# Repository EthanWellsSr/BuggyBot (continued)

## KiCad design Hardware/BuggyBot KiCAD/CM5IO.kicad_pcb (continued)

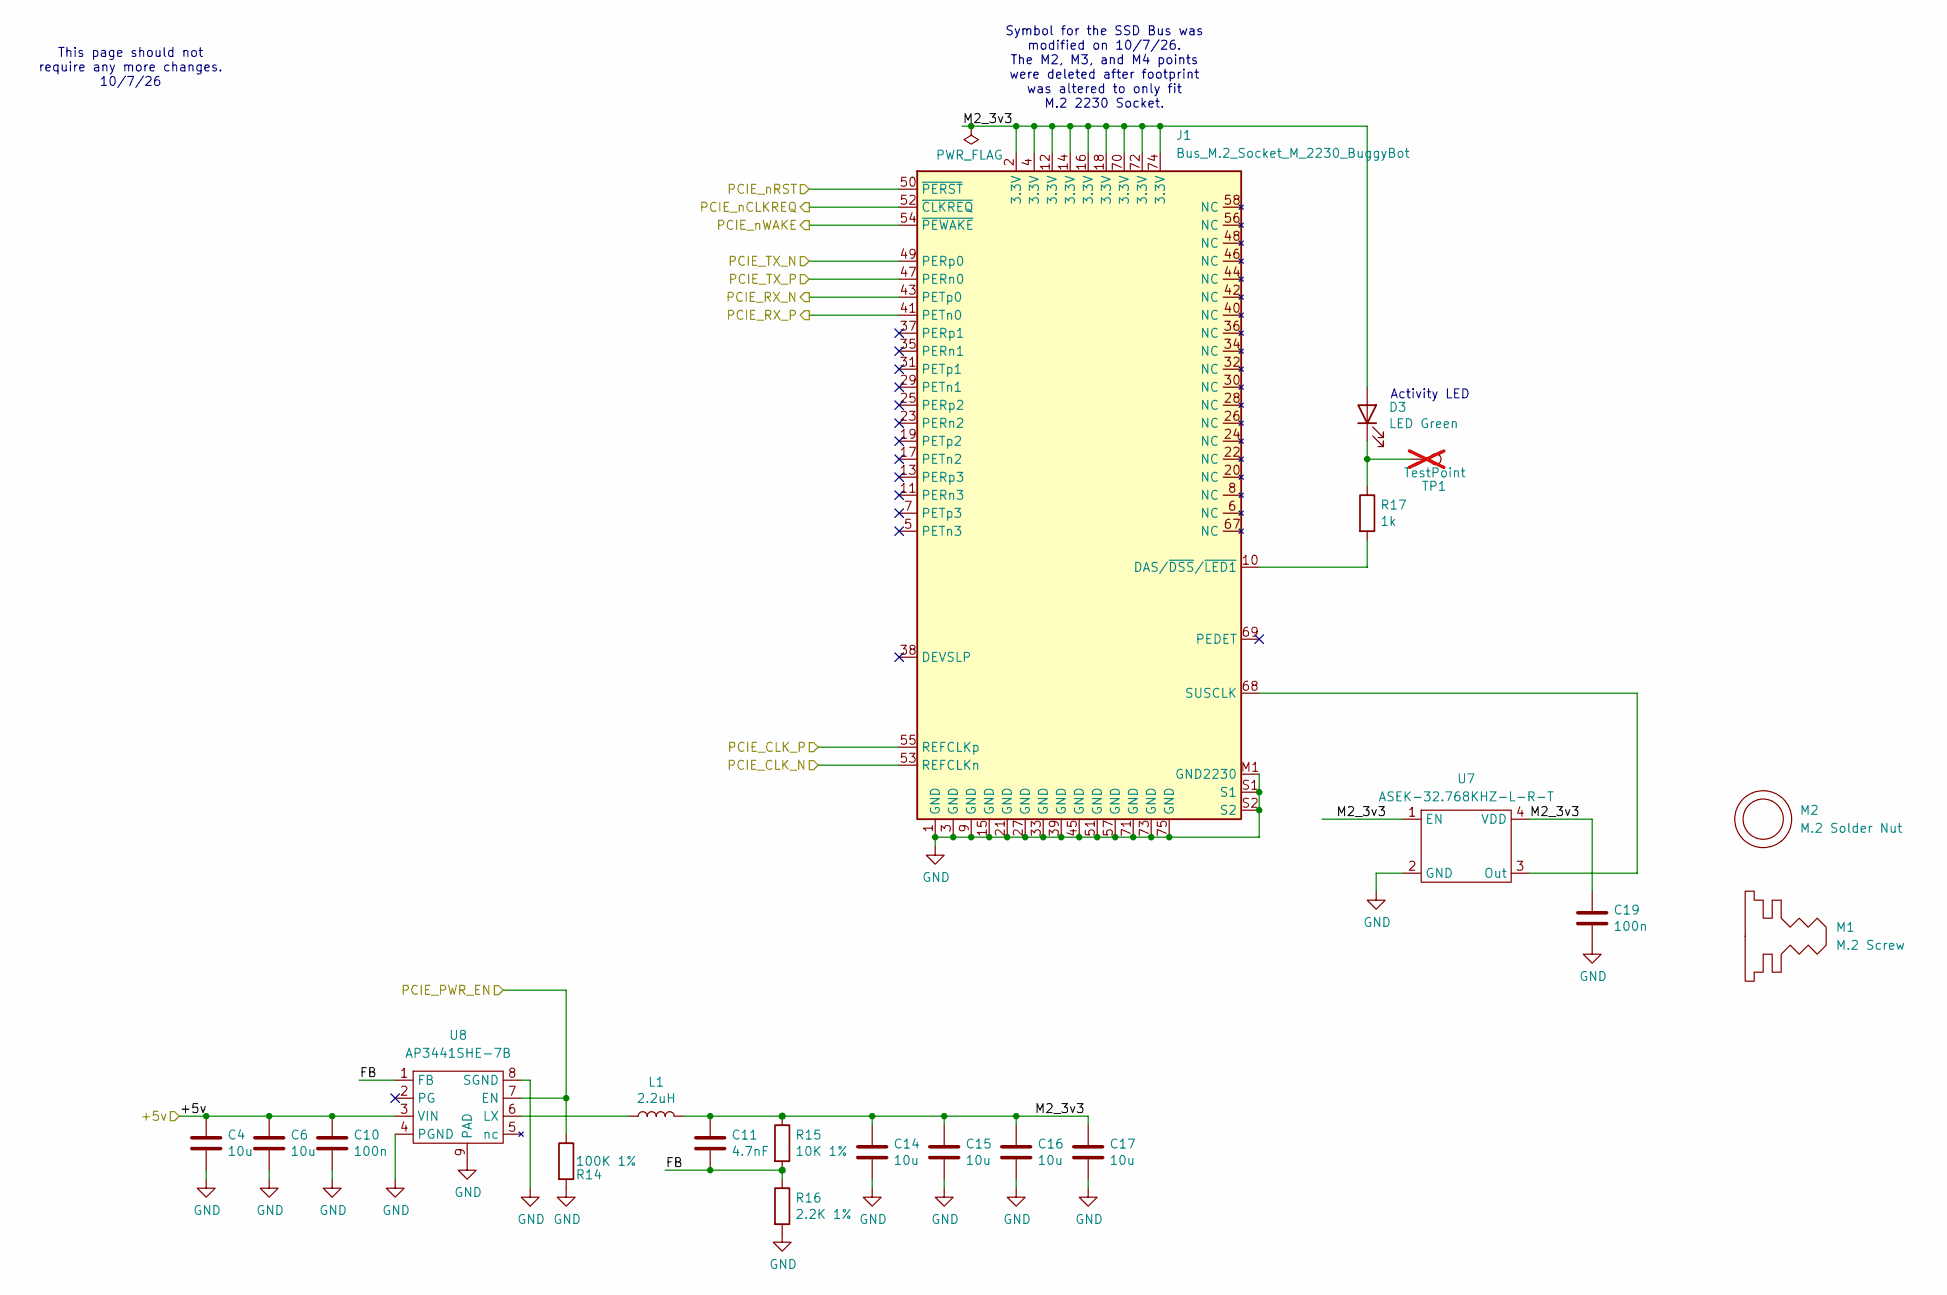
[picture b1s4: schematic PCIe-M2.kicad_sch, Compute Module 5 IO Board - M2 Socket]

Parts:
C4, C6, C14, C15, C16, C17: 10u; C_0805_2012Metric; Part Description 10uF 10% 10V Ceramic Capacitor X7R 0805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
C10, C19: 100n; C_0402_1005Metric; Part Description 0.1uF 10% 16V Ceramic Capacitor X7R 040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
C11: 4.7nF; C_0402_1005Metric; Part Description 4.7nF capacitor 0402
D3: LED Green; LED_0603_1608Metric; Part Description Green 572nm LED Indication - Discrete 2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
J1: Bus_M.2_Socket_M_2230_BuggyBot; M2_M_Key_2230_BuggyBot
L1: 2.2uH; L_Bourns_SRP5030CC; Part Description Inductor, SMT, 2520, 2u2, IRMS=7A, ISAT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
M1: M.2 Screw; Part Description M.2 Screw
M2: M.2 Solder Nut; Part Description Solder nut for M.2 slot
R14: 100K 1%; R_0402_1005Metric; Part Description Resistor 100K M1005 1% 63mW
R15: 10K 1%; R_0402_1005Metric; Part Description Resistor 10K M1005 1% 63mW
R16: 2.2K 1%; R_0402_1005Metric; Part Description Resistor 2.2K M1005 1% 63mW
R17: 1k; R_0402_1005Metric; Part Description Resistor 1K M1005 1% 63mW
TP1: TestPoint; TestPoint_Pad_2.0x2.0mm; Part Description Test point; not fitted
U7: ASEK-32.768KHZ-L-R-T; Crystal_SMD_3225-4Pin_3.2x2.5mm; Part Description 32KHz Xtal oscilator
U8: AP3441SHE-7B; DFN-8-1EP_2x2mm_P0.5mm_EP1.05x1.75mm; Part Description 3A DC-DC converter

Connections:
/+5v: C4.1, C6.1, C10.1, U8.3 (VIN); also elsewhere on the board
/CM5_HighSpeed/PCIE_CLK_N: J1.53 (REFCLKn); also elsewhere on the board
/CM5_HighSpeed/PCIE_CLK_P: J1.55 (REFCLKp); also elsewhere on the board
/CM5_HighSpeed/PCIE_PWR_EN: R14.1, U8.7 (EN); also elsewhere on the board
/CM5_HighSpeed/PCIE_RX_N: J1.43 (PETp0); also elsewhere on the board
/CM5_HighSpeed/PCIE_RX_P: J1.41 (PETn0); also elsewhere on the board
/CM5_HighSpeed/PCIE_TX_N: J1.49 (PERp0); also elsewhere on the board
/CM5_HighSpeed/PCIE_TX_P: J1.47 (PERn0); also elsewhere on the board
/CM5_HighSpeed/PCIE_nCLKREQ: J1.52 (~CLKREQ); also elsewhere on the board
/CM5_HighSpeed/PCIE_nRST: J1.50 (~PERST); also elsewhere on the board
/CM5_HighSpeed/PCIE_nWAKE: J1.54 (~PEWAKE); also elsewhere on the board
/PCIe-M2/FB: C11.2, R15.2, R16.1, U8.1 (FB)
/PCIe-M2/M2_3v3: C11.1, C14.1, C15.1, C16.1, C17.1, C19.1, D3.2 (A), J1.2 (3.3V), J1.4 (3.3V), J1.12 (3.3V), J1.14 (3.3V), J1.16 (3.3V), J1.18 (3.3V), J1.70 (3.3V), J1.72 (3.3V), J1.74 (3.3V), L1.2, R15.1, U7.1 (EN), U7.4 (VDD)
GND: C4.2, C6.2, C10.2, C14.2, C15.2, C16.2, C17.2, C19.2, J1.1 (GND), J1.3 (GND), J1.9 (GND), J1.15 (GND), J1.21 (GND), J1.27 (GND), J1.33 (GND), J1.39 (GND), J1.45 (GND), J1.51 (GND), J1.57 (GND), J1.71 (GND), J1.73 (GND), J1.75 (GND), J1.M1 (GND2230), J1.S1, J1.S2, R14.2, R16.2, U7.2 (GND), U8.4 (PGND), U8.8 (SGND), U8.9 (PAD); also elsewhere on the board
unnamed: D3.1 (K), R17.1, TP1.1 (1_1)
unnamed: J1.10 (DAS/~DSS/~LED1), R17.2
unnamed: J1.68 (SUSCLK), U7.3 (Out)
unnamed: L1.1, U8.6 (LX)

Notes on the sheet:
Symbol for the SSD Bus was modified on 10/7/26. The M2, M3, and M4 points were deleted after footprint was altered to only fit M.2 2230 Socket.
Activity LED
This page should not require any more changes. 10/7/26

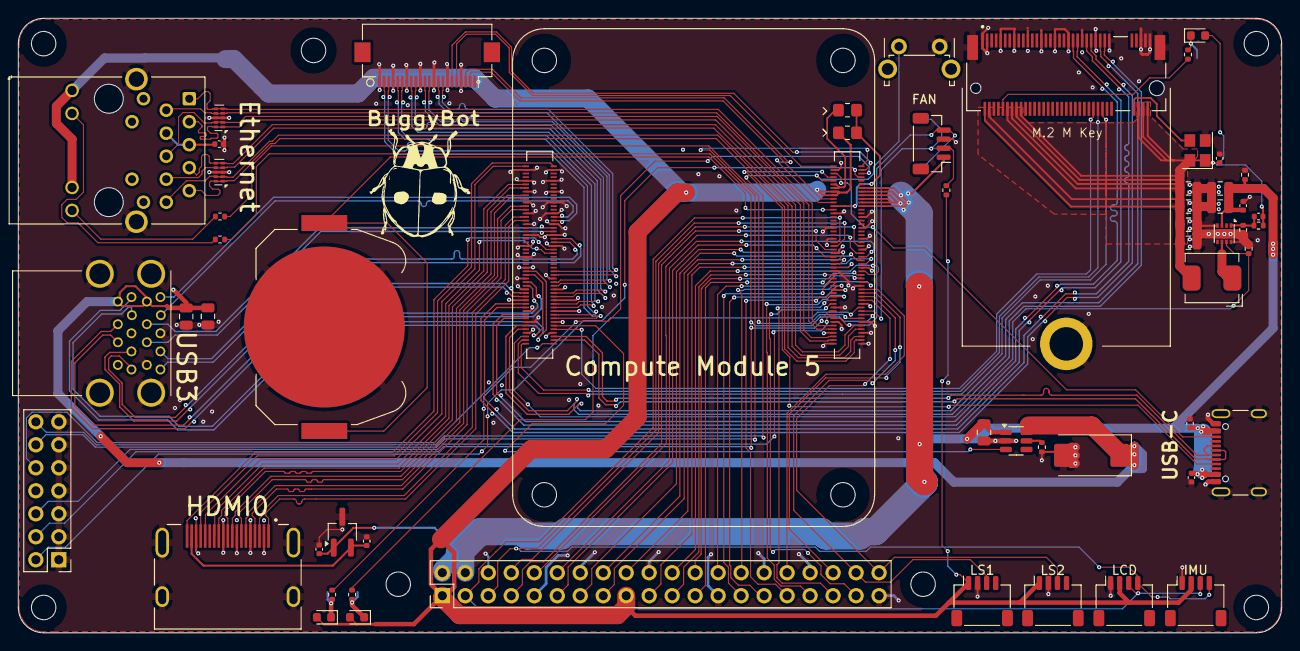
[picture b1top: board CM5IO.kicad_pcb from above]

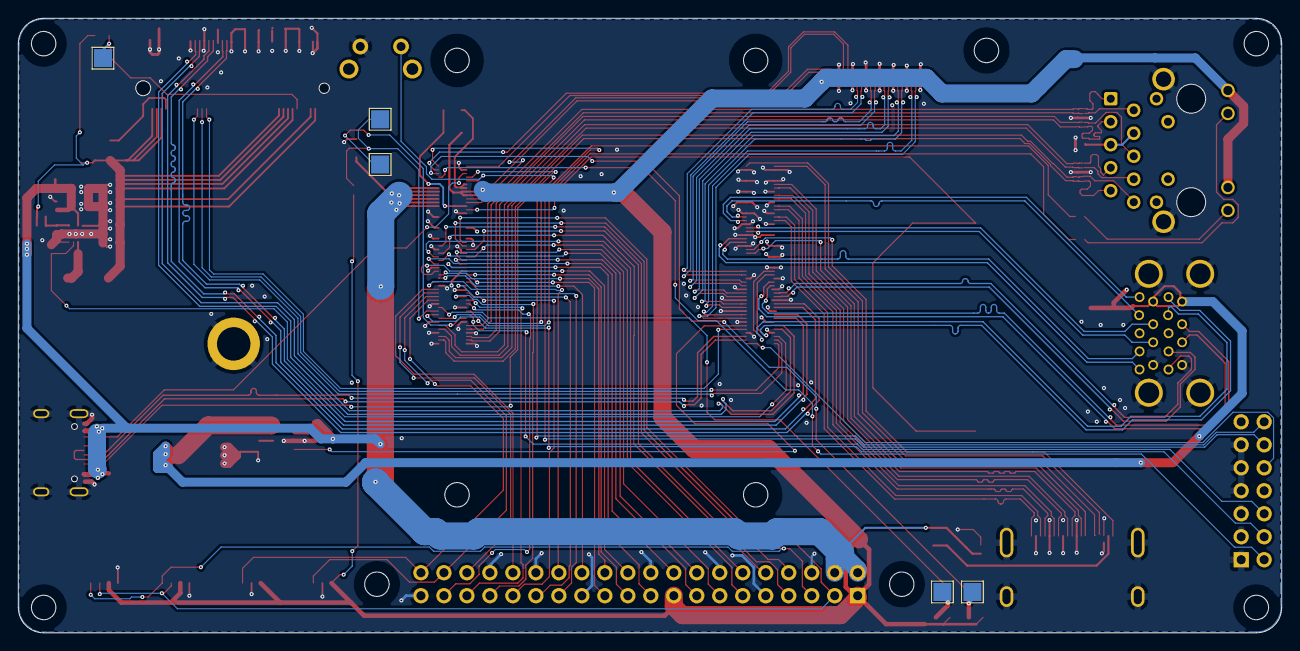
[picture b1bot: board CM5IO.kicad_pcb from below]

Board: 4 copper layers, 139.6 x 67.9 mm, 69 parts (5 on the bottom side), 121 nets.

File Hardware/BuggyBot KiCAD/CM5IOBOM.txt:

"Id";"Designator";"Footprint";"Quantity";"Designation";"Supplier and ref";
1;"BT1";"BatteryHolder_Keystone_3034_1x20mm";1;"Battery_Cell";;;
2;"SW1";"SW_Tactile_SPST_Angled_PTS645Vx39-2LFS";1;"Right angle Tact button";;;
3;"C1,C12,C13,C10,C18,C9,C19";"C_0402_1005Metric";7;"100n";;;
4;"C5,C6,C16,C8,C2,C17,C7,C15,C14,C4";"C_0805_2012Metric";10;"10u";;;
5;"J5,J16";"Hirose_FH12-22S-0.5SH_1x22-1MP_P0.50mm_Horizontal";2;"Conn_01x22_Female";;;
6;"R10,R1,R17";"R_0402_1005Metric";3;"1k";;;
7;"U1,U2";"USON-10_2.5x1.0mm_P0.5mm";2;"TPD4EUSB30";;;
8;"U12";"TSOT-23_HandSoldering";1;"RT9742SNGV";;;
9;"J8";"PinHeader_2x20_P2.54mm_Vertical";1;"THD-20-R";;;
10;"D2,D3";"LED_0603_1608Metric";2;"LED Green";;;
11;"R3,R2";"R_0402_1005Metric";2;"470R";;;
12;"J9,J6";"PinHeader_2x02_P2.54mm_Vertical";2;"THD-02-R";;;
13;"J11";"USB_C_Receptacle_GCT_USB4105-xx-A_16P_TopMnt_Horizontal";1;"USB_C_Receptacle_USB2.0";;;
14;"D1";"LED_0603_1608Metric";1;"LED Red";;;
15;"U5";"SOT-353_SC-70-5";1;"74LVC1G07SE-7";;;
16;"U18";"SOT-23-5";1;"RT9742GGJ5";;;
17;"U3";"TRJG0926HENL";1;"MagJack-A70-112-331N126";;;
18;"J10,J22";"EDAC 690-019-298-412";2;"690-019-298-412";;;
19;"R6,R7,R8,R16";"R_0402_1005Metric";4;"2.2K 1%";;;
20;"J2";"PinHeader_2x07_P2.54mm_Vertical";1;"Conn_02x07_Odd_Even";;;
21;"R5";"R_0805_2012Metric_Pad1.20x1.40mm_HandSolder";1;"0R";;;
22;"U8";"DFN-8-1EP_2x2mm_P0.5mm_EP1.05x1.75mm";1;"AP3441SHE-7B";;;
23;"J7";"SDCARD_MOLEX_503398-1892";1;"Micro_SD_Card_Det";;;
24;"J4";"M.2 M Key socket";1;"Bus_M.2_Socket_M";;;
25;"C11";"C_0402_1005Metric";1;"4.7nF";;;
26;"J12";"MTCONN_UBAF30-D2011";1;"USB3_A";;;
27;"J14";"JST_SH_BM04B-SRSS-TB_1x04-1MP_P1.00mm_Vertical";1;"JST_SHBM04B-SRSS-TB";;;
28;"C3";"CP_EIA-7343-31_Kemet-D";1;"100uF";;;
29;"U7";"Crystal_SMD_3225-4Pin_3.2x2.5mm";1;"ASEK-32.768KHZ-L-R-T";;;
30;"U6";"SOT-23-6";1;"AP22653W6";;;
31;"L1";"L_Bourns_SRP5030CC";1;"2.2uH";;;
32;"R15";"R_0402_1005Metric";1;"10K 1%";;;
33;"R12";"R_0402_1005Metric";1;"15K 1%";;;
34;"R14";"R_0402_1005Metric";1;"100K 1%";;;
35;"Module1";"Raspberry-Pi-5-Compute-Module";1;"ComputeModule5-CM5";;;
